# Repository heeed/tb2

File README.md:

# TerrierBot2

Code repository for the Terrierbot2...this years entry into the [Piwars](https://piwars.org/)

<hr>
Unless otherwise stated all contents are licensed under a MIT licence

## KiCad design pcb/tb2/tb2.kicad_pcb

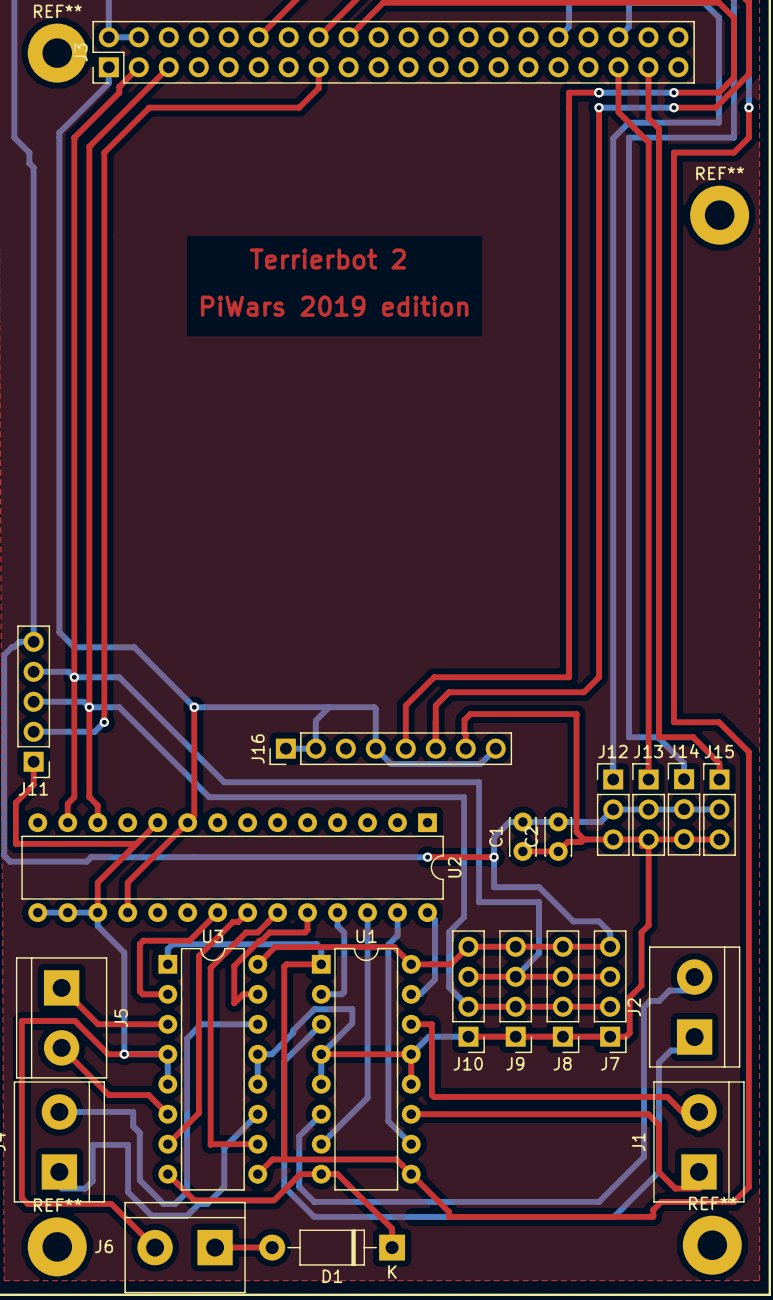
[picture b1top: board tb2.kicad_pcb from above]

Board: 2 copper layers, 22 parts (0 on the bottom side), 31 nets.

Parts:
C1, C2: 104; C_Disc_D3.0mm_W2.0mm_P2.50mm
D1: 1N5817; D_DO-41_SOD81_P10.16mm_Horizontal
J1: Motor1; TerminalBlock_bornier-2_P5.08mm
J2: Motor2; TerminalBlock_bornier-2_P5.08mm
J3: RPI GPIO; PinHeader_2x20_P2.54mm_Vertical
J4: Motor3; TerminalBlock_bornier-2_P5.08mm
J5: Motor4; TerminalBlock_bornier-2_P5.08mm
J6: Motor_Power; TerminalBlock_bornier-2_P5.08mm
J7: I2C 1; PinHeader_1x04_P2.54mm_Vertical
J8: I2C 2; PinHeader_1x04_P2.54mm_Vertical
J9: I2C 3; PinHeader_1x04_P2.54mm_Vertical
J10: I2C 4; PinHeader_1x04_P2.54mm_Vertical
J11: TOF_HEADER; PinHeader_1x05_P2.54mm_Vertical
J12: GVS1; PinHeader_1x03_P2.54mm_Vertical
J13: GVS2; PinHeader_1x03_P2.54mm_Vertical
J14: GVS3; PinHeader_1x03_P2.54mm_Vertical
J15: GVS4; PinHeader_1x03_P2.54mm_Vertical
J16: GY-BNOD55; PinHeader_1x08_P2.54mm_Vertical
U1, U3: L293D; DIP-16_W7.62mm
U2: MCP23017_SP; DIP-28_W7.62mm

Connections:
+3V3: J3.1, J3.17, J16.1, J16.2, J16.4, J16.8, U2.9, U2.18
+5V: C1.2, C2.2, J3.2, J3.4, J7.4, J8.4, J9.4, J10.4, J11.5, J12.2, J13.2, J14.2, J15.2, U1.16, U3.16
+BATT: D1.1, U1.8, U3.8
/GVS1: J3.36, J12.1
/GVS2: J3.32, J14.1
/GVS3: J3.35, J13.1
/GVS4: J3.37, J15.1
/PWM0: J3.12, U1.1, U1.9, U3.1, U3.9
/SCL: J3.5, J7.2, J8.2, J9.2, J10.2, J11.3, U2.12
/SCL_SOFT: J3.18, J16.5
/SDA: J3.3, J7.3, J8.3, J9.3, J10.3, J11.4, U2.13
/SDA_SOFT: J3.16, J16.6
/TOF_INT: J3.15, J11.2
GND: C1.1, C2.1, J3.6, J3.9, J3.14, J3.20, J3.25, J3.30, J3.34, J3.39, J6.2, J7.1, J8.1, J9.1, J10.1, J11.1, J12.3, J13.3, J14.3, J15.3, J16.7, U1.4, U1.5, U1.12, U1.13, U2.10, U2.15, U2.16, U2.17, U3.4, U3.5, U3.12, U3.13
unnamed: D1.2, J6.1
unnamed: J1.1, U1.11
unnamed: J1.2, U1.14
unnamed: J2.1, U1.3
unnamed: J2.2, U1.6
unnamed: J4.1, U3.11
unnamed: J4.2, U3.14
unnamed: J5.1, U3.3
unnamed: J5.2, U3.6
unnamed: U1.2, U2.25
unnamed: U1.7, U2.26
unnamed: U1.10, U2.27
unnamed: U1.15, U2.28
unnamed: U2.21, U3.2
unnamed: U2.22, U3.7
unnamed: U2.23, U3.10
unnamed: U2.24, U3.15

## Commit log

2018-10-12 Initial Commit - First dump of documentation and notes
2018-12-26 Initial commit of the movement class. Using STS-Pi for a test rig.
    Robot currently able to drive forwards/backwards/left and right
2018-12-29 Adding in VL53L1X support
2019-01-01 Create LICENSE
    Adding License before going public
2019-01-01 Adding RobotDrive.py
    Allows simple WASD control of the bot and 'x' to stop
2019-03-29 Branch and files for TB2 rebuild and competition
2019-12-22 adding pcb files for future potenitals
2020-10-21 Removing errant spaces/tabs to get tb2 working again
